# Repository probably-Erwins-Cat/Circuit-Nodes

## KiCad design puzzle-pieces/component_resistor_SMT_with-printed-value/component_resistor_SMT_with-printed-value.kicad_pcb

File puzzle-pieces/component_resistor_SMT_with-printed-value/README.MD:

# Resistor (SMT) — printed value set

This set provides SMT resistor footprints with the resistance value printed on the silkscreen. It is convenient for classroom kits where students should quickly identify the mounted value without reading tiny SMD markings.

## Typical uses in circuits
- The same as other resistors: current limiting, voltage division, and basic signal conditioning. The printed values simply make identification easier in teaching contexts.

## Practical and safety notes
- Power dissipation: calculate with
	\[P = U \cdot I = I^2 \cdot R = \dfrac{U^2}{R}.\]
	Check that the selected package and resistor power rating suit your experiment.

## E-series and kit guidance
- Use E-series preferred values (E12/E24) to plan a compact kit. Keep a selection of common values such as 100 Ω, 330 Ω, 1 kΩ, 10 kΩ to support typical classroom activities.

See Wikipedia for more on E-series: https://en.wikipedia.org/wiki/E_series_of_preferred_numbers

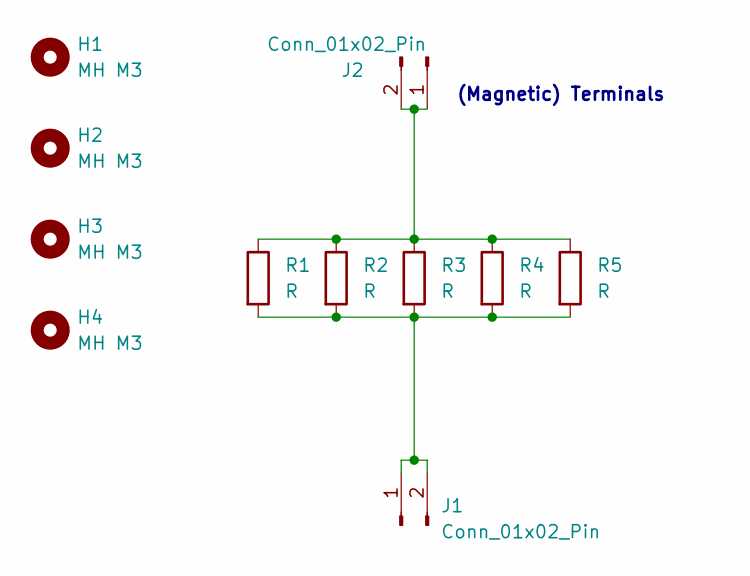
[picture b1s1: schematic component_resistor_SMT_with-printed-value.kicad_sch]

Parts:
H1, H2, H3, H4: MH M3; MountingHole_3.0mm_M3_tight
J1, J2: Conn_01x02_Pin; Magentic_Connector_1x02_P2.5mm_Horizontal
R1: R; R_2512_6332Metric
R2: R; R_2010_5025Metric
R3: R; R_1210_3225Metric
R4: R; R_1206_3216Metric
R5: R; R_0805_2012Metric

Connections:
unnamed: J2.1, J2.2, R1.1, R2.1, R3.1, R4.1, R5.1
NordSued: J1.1, J1.2, R1.2, R2.2, R3.2, R4.2, R5.2

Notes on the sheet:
(Magnetic) Terminals

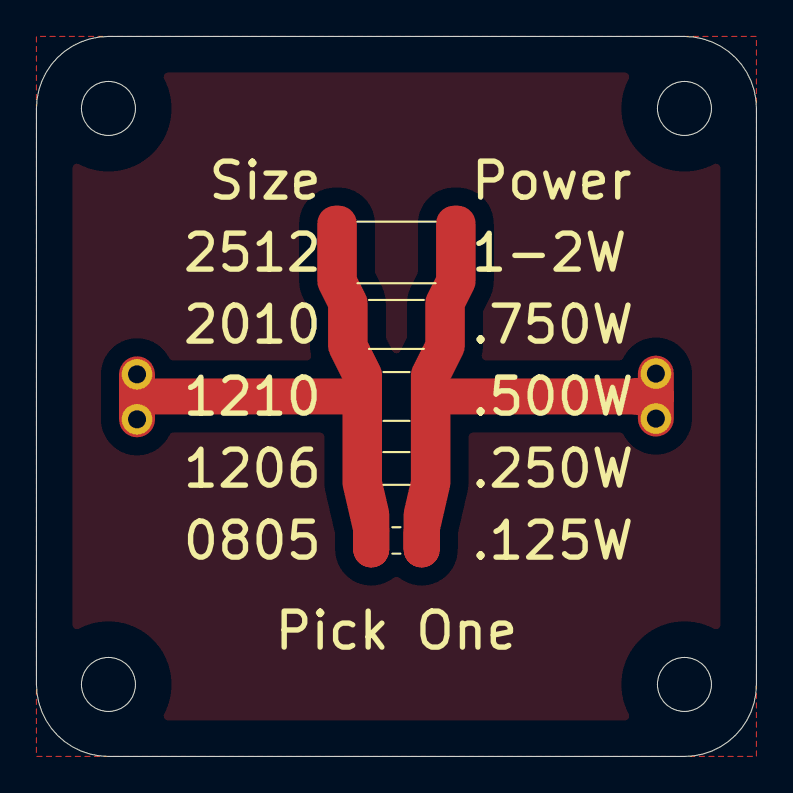
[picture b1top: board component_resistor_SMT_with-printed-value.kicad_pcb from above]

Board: 2 copper layers, 40.0 x 40.0 mm, 11 parts (0 on the bottom side), 2 nets.

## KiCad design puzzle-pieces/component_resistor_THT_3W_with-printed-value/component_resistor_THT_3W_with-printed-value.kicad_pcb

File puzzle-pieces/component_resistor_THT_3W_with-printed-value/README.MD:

# Resistor (THT, printed value set)

This set provides THT resistors with values printed on the silkscreen for easy identification in classroom kits. Use these when learners should quickly identify component values without reading small SMD markings.

## Typical uses in circuits
- The same uses as standard resistors: current limiting, voltage division, signal conditioning, and power-dissipation demonstrations.

## Practical and safety notes
- Power dissipation: calculate with
	\[P = U \cdot I = I^2 \cdot R = \dfrac{U^2}{R}\]
	Ensure the chosen resistor wattage (e.g., 3 W) is adequate for the experiment.

## E-series and kit recommendations
- Prefer standard E-series values (E3/E6) when planning kits. Keep a selection that spans from a hundred ohms to 1 MΩ for diverse classroom experiments.

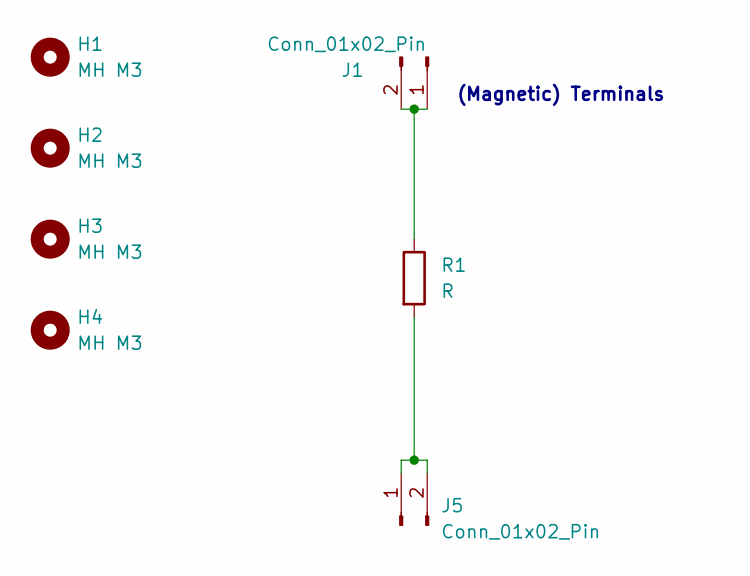
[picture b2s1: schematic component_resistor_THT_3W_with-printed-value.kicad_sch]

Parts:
H1, H2, H3, H4: MH M3; MountingHole_3.0mm_M3_tight
J1, J5: Conn_01x02_Pin; Magentic_Connector_1x02_P2.5mm_Horizontal
R1: R; R_Axial_DIN0411_L9.9mm_D3.6mm_P20.32mm_Horizontal

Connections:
unnamed: J1.1, J1.2, R1.1
unnamed: J5.1, J5.2, R1.2

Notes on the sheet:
(Magnetic) Terminals

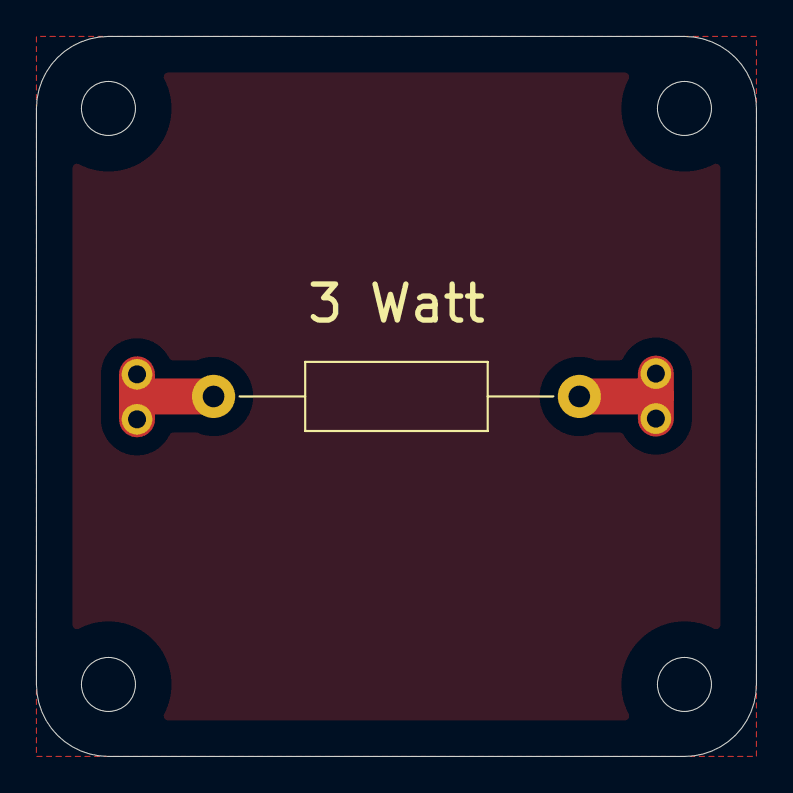
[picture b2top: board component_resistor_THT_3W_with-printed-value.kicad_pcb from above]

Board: 2 copper layers, 40.0 x 40.0 mm, 7 parts (0 on the bottom side), 2 nets.

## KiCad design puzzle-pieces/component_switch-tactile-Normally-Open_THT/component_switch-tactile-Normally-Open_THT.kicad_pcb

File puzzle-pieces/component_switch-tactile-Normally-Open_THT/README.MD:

# Tactile Switch - Normally Open

A 12 x 12 mm tactileswitch footprint for components that are *normally open* (NO) when not actuated. These switches close the circuit when pressed and are useful for momentary inputs and simple controls.

## Compatible Components and Usage

Virtually all tactile switches with 12 x 12 mm footprint and THT are compatible. Cheap, no-name tactile switches are sufficient. If you prefer color-coordinated switches with higher durability, look for Omron switches. They come in different colors and are more robust.

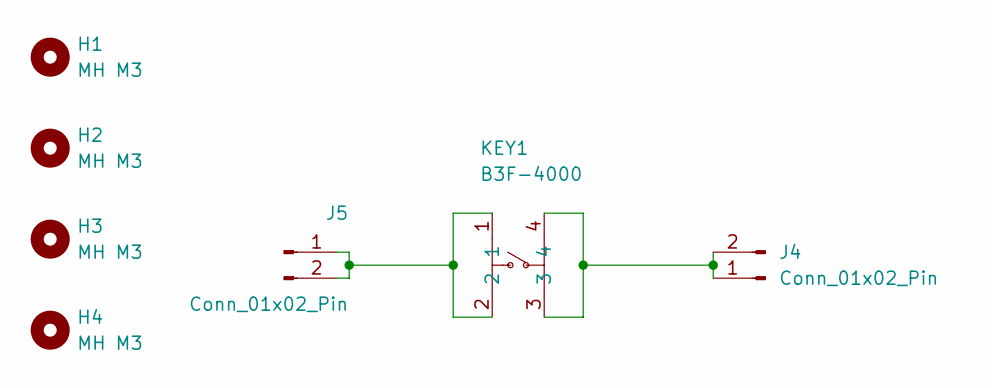
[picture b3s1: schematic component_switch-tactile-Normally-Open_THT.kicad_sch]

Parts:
H1, H2, H3, H4: MH M3; MountingHole_3.0mm_M3_tight
J4, J5: Conn_01x02_Pin; Magnetic_Connector_1x02_P2.5mm_Horizontal_round-ears
KEY1: B3F-4000; KEY-TH_4P-L12.0-W12.0-P5.00-LS13.4-EH; LCSC Part C87494

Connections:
unnamed: J4.1, J4.2, KEY1.3, KEY1.4
unnamed: J5.1, J5.2, KEY1.1, KEY1.2

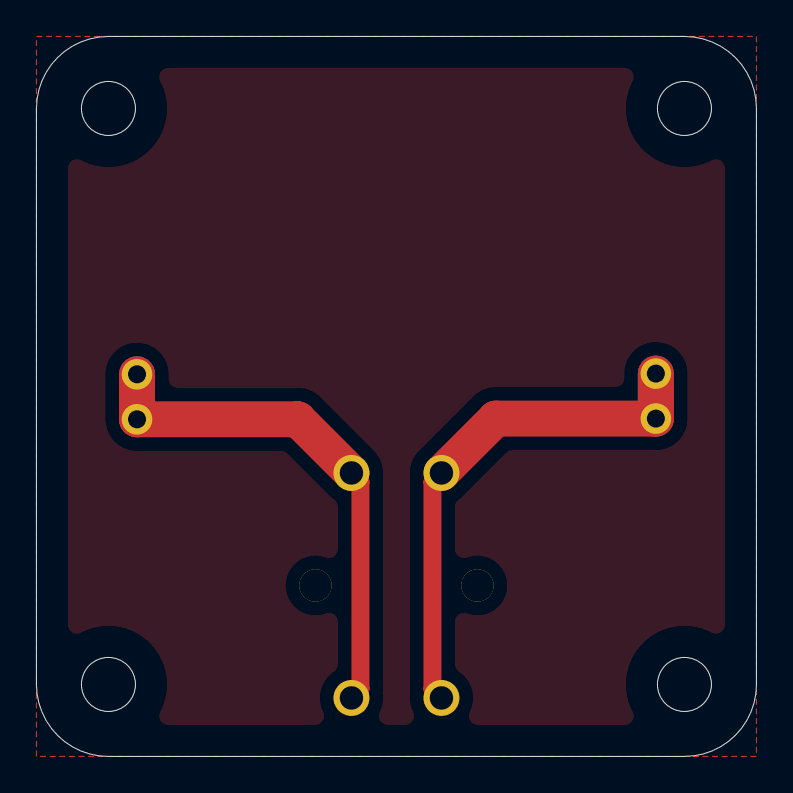
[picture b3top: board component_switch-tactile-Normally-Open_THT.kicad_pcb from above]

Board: 2 copper layers, 40.0 x 40.0 mm, 7 parts (1 on the bottom side), 2 nets.
